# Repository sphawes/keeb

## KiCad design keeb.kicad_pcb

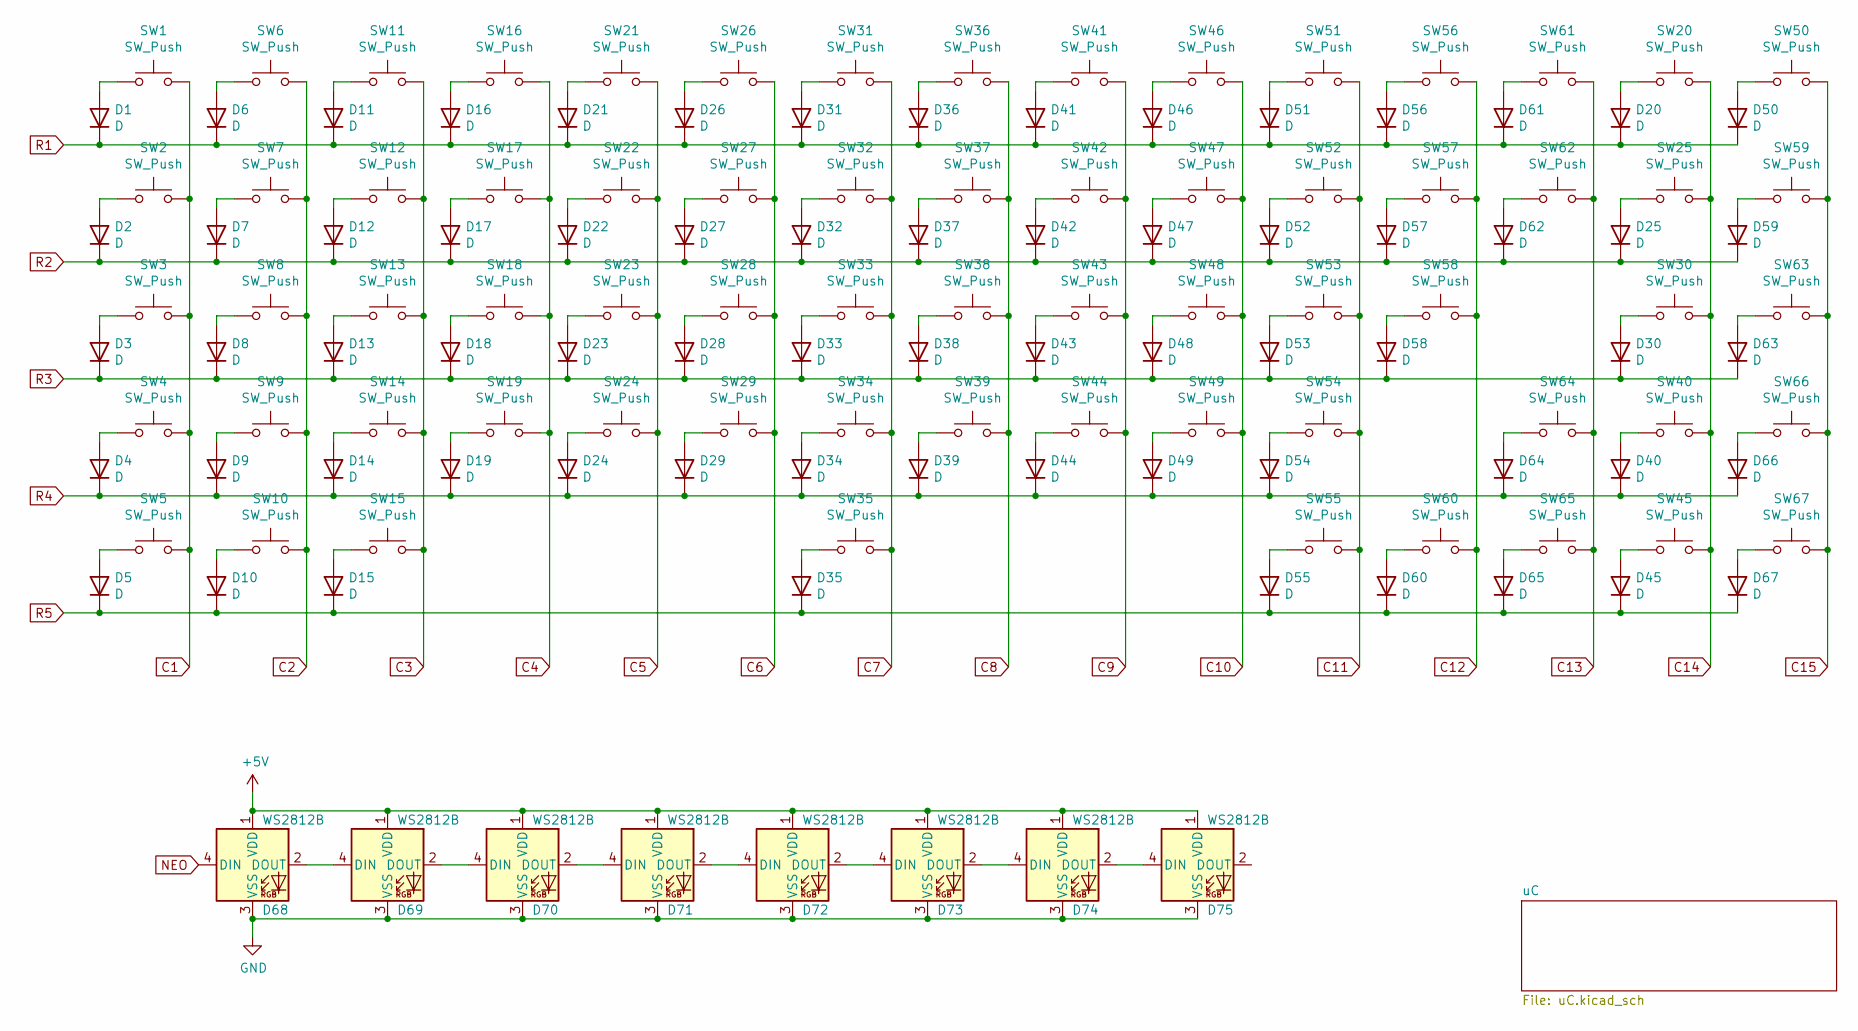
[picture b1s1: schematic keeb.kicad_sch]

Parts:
D1, D2, D3, D4, D5, D6, D7, D8, D9, D10, D11, D12, D13, D14, D15, D16, D17, D18, D19, D20, D21, D22, D23, D24, D25, D26, D27, D28, D29, D30, D31, D32, D33, D34, D35, D36, D37, D38, D39, D40, D41, D42, D43, D44, D45, D46, D47, D48, D49, D50, D51, D52, D53, D54, D55, D56, D57, D58, D59, D60, D61, D62, D63, D64, D65, D66, D67: D; D_SOD-123
D68, D69, D70, D71, D72, D73, D74, D75: WS2812B; LED_WS2812B_PLCC4_5.0x5.0mm_P3.2mm
SW1, SW6, SW7, SW8, SW9, SW11, SW12, SW13, SW14, SW16, SW17, SW18, SW19, SW21, SW22, SW23, SW24, SW26, SW27, SW28, SW29, SW31, SW32, SW33, SW34, SW36, SW37, SW38, SW39, SW40, SW41, SW42, SW43, SW44, SW45, SW46, SW47, SW48, SW49, SW50, SW51, SW52, SW53, SW54, SW56, SW57, SW58, SW59, SW61, SW62, SW63, SW65, SW66, SW67: SW_Push; SW_Hotswap_Kailh_Choc_V1_plated_1.00u
SW2, SW25, SW55, SW60: SW_Push; SW_Hotswap_Kailh_Choc_V1_plated_1.50u
SW3, SW64: SW_Push; SW_Hotswap_Kailh_Choc_V1_plated_1.75u
SW4, SW30: SW_Push; SW_Hotswap_Kailh_Choc_V1_plated_2.25u
SW5, SW10, SW15: SW_Push; SW_Hotswap_Kailh_Choc_V1_plated_1.25u
SW20: SW_Push; SW_Hotswap_Kailh_Choc_V1V2_Plated_2.00u
SW35: SW_Push; SW_Hotswap_Kailh_Choc_V1V2_Plated_2.50u

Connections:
+5V: D68.1 (VDD), D69.1 (VDD), D70.1 (VDD), D71.1 (VDD), D72.1 (VDD), D73.1 (VDD), D74.1 (VDD), D75.1 (VDD)
C1: SW1.2, SW2.2, SW3.2, SW4.2, SW5.2
C2: SW6.2, SW7.2, SW8.2, SW9.2, SW10.2
C3: SW11.2, SW12.2, SW13.2, SW14.2, SW15.2
C4: SW16.2, SW17.2, SW18.2, SW19.2
C5: SW21.2, SW22.2, SW23.2, SW24.2
C6: SW26.2, SW27.2, SW28.2, SW29.2
C7: SW31.2, SW32.2, SW33.2, SW34.2, SW35.2
C8: SW36.2, SW37.2, SW38.2, SW39.2
C9: SW41.2, SW42.2, SW43.2, SW44.2
C10: SW46.2, SW47.2, SW48.2, SW49.2
C11: SW51.2, SW52.2, SW53.2, SW54.2, SW55.2
C12: SW56.2, SW57.2, SW58.2, SW60.2
C13: SW61.2, SW62.2, SW64.2, SW65.2
C14: SW20.2, SW25.2, SW30.2, SW40.2, SW45.2
C15: SW50.2, SW59.2, SW63.2, SW66.2, SW67.2
GND: D68.3 (VSS), D69.3 (VSS), D70.3 (VSS), D71.3 (VSS), D72.3 (VSS), D73.3 (VSS), D74.3 (VSS), D75.3 (VSS)
NEO: D68.4 (DIN)
unnamed: D1.2 (A), SW1.1
unnamed: D2.2 (A), SW2.1
unnamed: D3.2 (A), SW3.1
unnamed: D4.2 (A), SW4.1
unnamed: D5.2 (A), SW5.1
unnamed: D6.2 (A), SW6.1
unnamed: D7.2 (A), SW7.1
unnamed: D8.2 (A), SW8.1
unnamed: D9.2 (A), SW9.1
unnamed: D10.2 (A), SW10.1
unnamed: D11.2 (A), SW11.1
unnamed: D12.2 (A), SW12.1
unnamed: D13.2 (A), SW13.1
unnamed: D14.2 (A), SW14.1
unnamed: D15.2 (A), SW15.1
unnamed: D16.2 (A), SW16.1
unnamed: D17.2 (A), SW17.1
unnamed: D18.2 (A), SW18.1
unnamed: D19.2 (A), SW19.1
unnamed: D20.2 (A), SW20.1
unnamed: D21.2 (A), SW21.1
unnamed: D22.2 (A), SW22.1
unnamed: D23.2 (A), SW23.1
unnamed: D24.2 (A), SW24.1
unnamed: D25.2 (A), SW25.1
unnamed: D26.2 (A), SW26.1
unnamed: D27.2 (A), SW27.1
unnamed: D28.2 (A), SW28.1
unnamed: D29.2 (A), SW29.1
unnamed: D30.2 (A), SW30.1
unnamed: D31.2 (A), SW31.1
unnamed: D32.2 (A), SW32.1
unnamed: D33.2 (A), SW33.1
unnamed: D34.2 (A), SW34.1
unnamed: D35.2 (A), SW35.1
unnamed: D36.2 (A), SW36.1
unnamed: D37.2 (A), SW37.1
unnamed: D38.2 (A), SW38.1
unnamed: D39.2 (A), SW39.1
unnamed: D40.2 (A), SW40.1
unnamed: D41.2 (A), SW41.1
unnamed: D42.2 (A), SW42.1
unnamed: D43.2 (A), SW43.1
unnamed: D44.2 (A), SW44.1
unnamed: D45.2 (A), SW45.1
unnamed: D46.2 (A), SW46.1
unnamed: D47.2 (A), SW47.1
unnamed: D48.2 (A), SW48.1
unnamed: D49.2 (A), SW49.1
unnamed: D50.2 (A), SW50.1
unnamed: D51.2 (A), SW51.1
unnamed: D52.2 (A), SW52.1
unnamed: D53.2 (A), SW53.1
unnamed: D54.2 (A), SW54.1
unnamed: D55.2 (A), SW55.1
unnamed: D56.2 (A), SW56.1
unnamed: D57.2 (A), SW57.1
unnamed: D58.2 (A), SW58.1
unnamed: D59.2 (A), SW59.1
unnamed: D60.2 (A), SW60.1
unnamed: D61.2 (A), SW61.1
unnamed: D62.2 (A), SW62.1
unnamed: D63.2 (A), SW63.1
unnamed: D64.2 (A), SW64.1
unnamed: D65.2 (A), SW65.1
unnamed: D66.2 (A), SW66.1
unnamed: D67.2 (A), SW67.1
unnamed: D68.2 (DOUT), D69.4 (DIN)
unnamed: D69.2 (DOUT), D70.4 (DIN)
unnamed: D70.2 (DOUT), D71.4 (DIN)
unnamed: D71.2 (DOUT), D72.4 (DIN)
unnamed: D72.2 (DOUT), D73.4 (DIN)
unnamed: D73.2 (DOUT), D74.4 (DIN)
unnamed: D74.2 (DOUT), D75.4 (DIN)
R1: D1.1 (K), D6.1 (K), D11.1 (K), D16.1 (K), D20.1 (K), D21.1 (K), D26.1 (K), D31.1 (K), D36.1 (K), D41.1 (K), D46.1 (K), D50.1 (K), D51.1 (K), D56.1 (K), D61.1 (K)
R2: D2.1 (K), D7.1 (K), D12.1 (K), D17.1 (K), D22.1 (K), D25.1 (K), D27.1 (K), D32.1 (K), D37.1 (K), D42.1 (K), D47.1 (K), D52.1 (K), D57.1 (K), D59.1 (K), D62.1 (K)
R3: D3.1 (K), D8.1 (K), D13.1 (K), D18.1 (K), D23.1 (K), D28.1 (K), D30.1 (K), D33.1 (K), D38.1 (K), D43.1 (K), D48.1 (K), D53.1 (K), D58.1 (K), D63.1 (K)
R4: D4.1 (K), D9.1 (K), D14.1 (K), D19.1 (K), D24.1 (K), D29.1 (K), D34.1 (K), D39.1 (K), D40.1 (K), D44.1 (K), D49.1 (K), D54.1 (K), D64.1 (K), D66.1 (K)
R5: D5.1 (K), D10.1 (K), D15.1 (K), D35.1 (K), D45.1 (K), D55.1 (K), D60.1 (K), D65.1 (K), D67.1 (K)

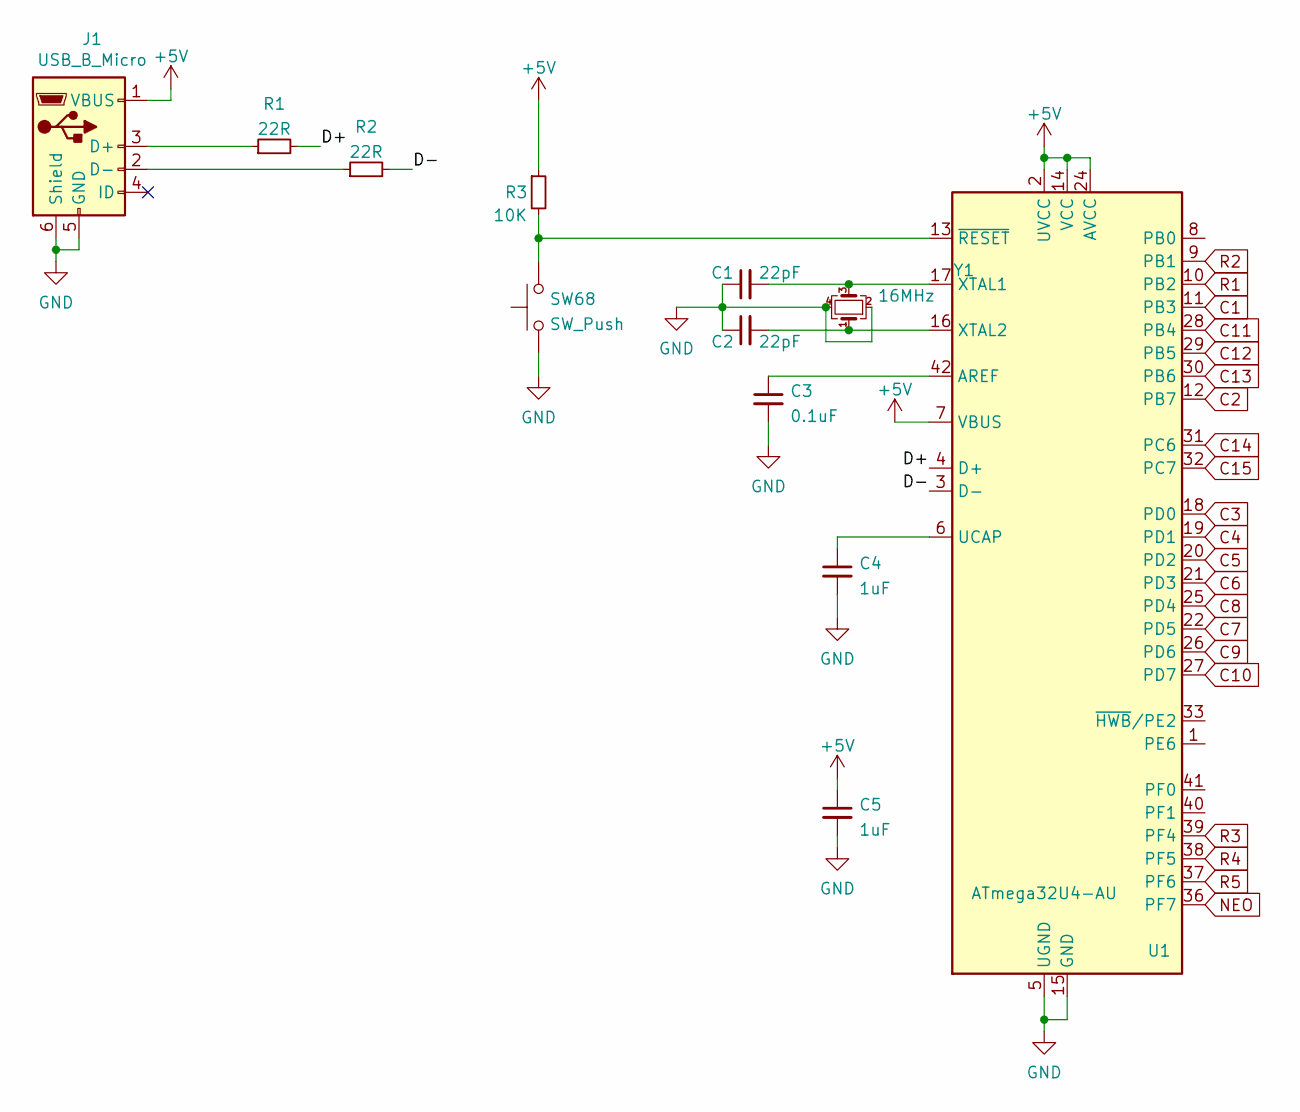
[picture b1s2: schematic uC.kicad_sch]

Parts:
C1, C2: 22pF; C_0805_2012Metric
C3: 0.1uF; C_0805_2012Metric
C4, C5: 1uF; C_0805_2012Metric
J1: USB_B_Micro; USB_Micro-B_Molex-105017-0001
R1, R2: 22R; R_0805_2012Metric
R3: 10K; R_0805_2012Metric
SW68: SW_Push; SW_SPST_PTS645
U1: ATmega32U4-AU; TQFP-44_10x10mm_P0.8mm
Y1: 16MHz; Crystal_SMD_Abracon_ABM8G-4Pin_3.2x2.5mm

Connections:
unnamed: J1.2 (D-), R2.1
unnamed: J1.3 (D+), R1.1
unnamed: R2.2, U1.3 (D-)
unnamed: R1.2, U1.4 (D+)
unnamed: C4.1, U1.6 (UCAP)
unnamed: R3.2, SW68.2, U1.13 (~RESET)
unnamed: C2.2, U1.16 (XTAL2), Y1.1
unnamed: C1.2, U1.17 (XTAL1), Y1.3
unnamed: C3.1, U1.42 (AREF)

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
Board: 2 copper layers, 144 parts (67 on the bottom side), 99 nets, no tracks yet.

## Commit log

2026-01-11 adds keeb
